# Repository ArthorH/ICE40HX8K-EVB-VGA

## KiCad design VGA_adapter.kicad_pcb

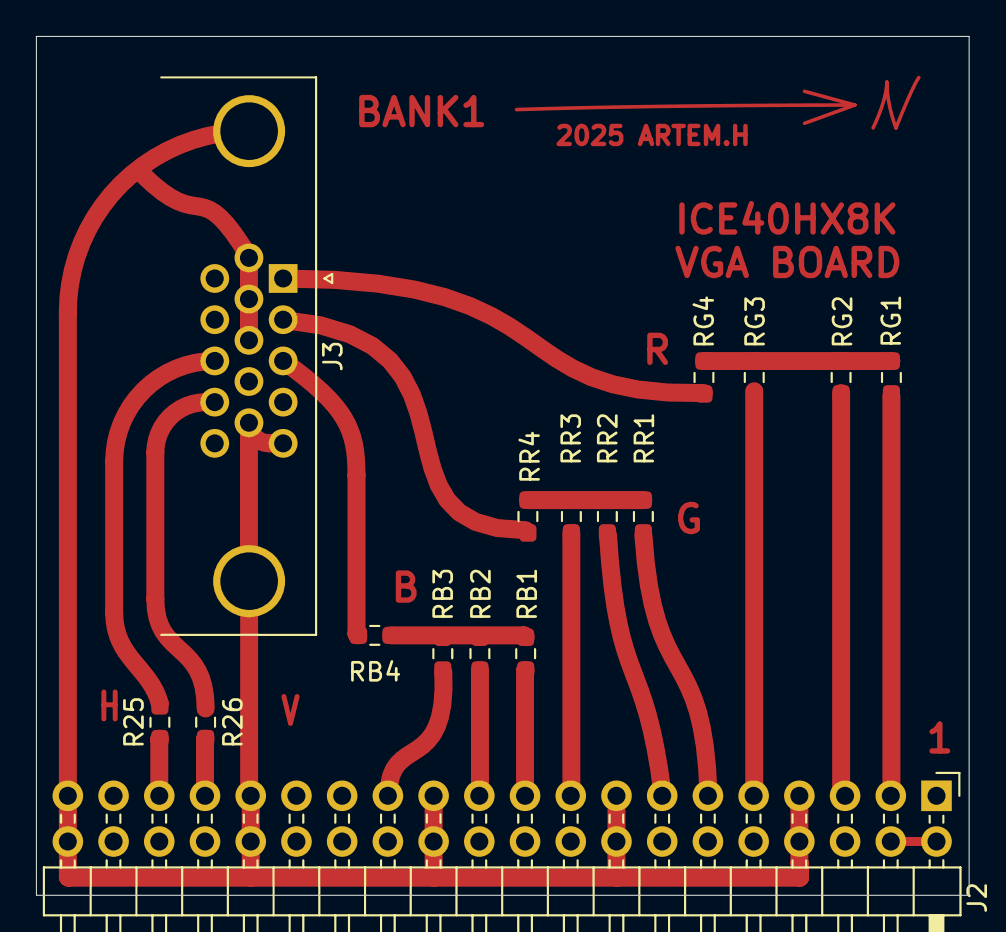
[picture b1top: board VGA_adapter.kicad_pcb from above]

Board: 2 copper layers, 51.8 x 47.7 mm, 16 parts (0 on the bottom side), 21 nets.

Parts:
J2: Header bank1; PinHeader_2x20_P2.54mm_Horizontal
J3: VGA; DSUB-15-HD_Pins_Horizontal_P2.29x1.90mm_EdgePinOffset3.03mm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
R25, R26: 49.9R; R_0603_1608Metric_Pad0.98x0.95mm_HandSolder
RB1: 2K2; R_0603_1608Metric_Pad0.98x0.95mm_HandSolder
RB2: 1K2; R_0603_1608Metric_Pad0.98x0.95mm_HandSolder
RB3: 560R; R_0603_1608Metric_Pad0.98x0.95mm_HandSolder
RB4: 75R; R_0603_1608Metric_Pad0.98x0.95mm_HandSolder
RG1: 2K2; R_0603_1608Metric_Pad0.98x0.95mm_HandSolder
RG2: 1K2; R_0603_1608Metric_Pad0.98x0.95mm_HandSolder
RG3: 560R; R_0603_1608Metric_Pad0.98x0.95mm_HandSolder
RG4: 75R; R_0603_1608Metric_Pad0.98x0.95mm_HandSolder
RR1: 2K2; R_0603_1608Metric_Pad0.98x0.95mm_HandSolder
RR2: 1K2; R_0603_1608Metric_Pad0.98x0.95mm_HandSolder
RR3: 560R; R_0603_1608Metric_Pad0.98x0.95mm_HandSolder
RR4: 75R; R_0603_1608Metric_Pad0.98x0.95mm_HandSolder

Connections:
/B: J3.3, RB4.2
/G: J3.2, RR4.2
/H_Sync: J2.18, R25.1
/PIO1_01: J2.2, RG1.1
/PIO1_03: J2.3, RG2.1
/PIO1_14: J2.5, RG3.1
/PIO1_16: J2.6, RR1.1
/PIO1_21: J2.7, RR2.1
/PIO1_22: J2.9, RR3.1
/PIO1_29: J2.11, RB2.1
/PIO1_32: J2.13, RB3.1
/PIO1_42: J2.10, RB1.1
/PIO1_44: J2.17, R26.1
/R: J3.1, RG4.2
GND: J2.4, J2.8, J2.12, J2.16, J2.20, J2.21, J2.25, J2.29, J2.33, J2.37, J3.0, J3.5, J3.6, J3.7, J3.8, J3.10
unnamed: J3.13, R25.2
unnamed: J3.14, R26.2
unnamed: RB1.2, RB2.2, RB3.2, RB4.1
unnamed: RG1.2, RG2.2, RG3.2, RG4.1
unnamed: RR1.2, RR2.2, RR3.2, RR4.1
VCC_1V2: J2.39, J2.40

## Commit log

2025-03-15 Inital commit
2025-03-17 Add SW archive
